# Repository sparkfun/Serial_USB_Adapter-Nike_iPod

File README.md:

**NOTE: This product has been retired from our catalog and is no longer for sale. This page is made available for those looking for datasheets and the simply curious.**

SparkFun Serial to USB Adapter - Nike+iPod
========================================

[*SparkFun Serial to USB Adapter - Nike+iPod (DEV-08245)*](https://www.sparkfun.com/products/8245)

This is a simple USB serial interface to mate with the Nike+iPod product. 
Use this breakout board to send and receive serial commands to the receiver and listen for individual foot pods. 
This will allow easy creation of proximity based projects and running/workout research. 
VCC (3.3V), ground, and iPod TX and RX are brought out to a standard header so that you can connect this board to a microcontroller.

Repository Contents
-------------------

* **/Firmware** - Example code 
* **/Hardware** - Eagle design files (.brd, .sch)
* **/Production** - Production panel files (.brd)

Documentation
--------------
* **[Hookup Guide](https://www.sparkfun.com/tutorials/41)** - Basic hookup guide for the adapter.
* **[SparkFun Fritzing repo](https://github.com/sparkfun/Fritzing_Parts)** - Fritzing diagrams for SparkFun products.
* **[SparkFun 3D Model repo](https://github.com/sparkfun/3D_Models)** - 3D models of SparkFun products. 

License Information
-------------------
This product is _**open source**_! 

The **hardware** is released under [Creative Commons ShareAlike 4.0 International](https://creativecommons.org/licenses/by-sa/4.0/).

Please use, reuse, and modify these files as you see fit. Please maintain attribution to SparkFun Electronics and release anything derivative under the same license.

Distributed as-is; no warranty is given.

- Your friends at SparkFun.

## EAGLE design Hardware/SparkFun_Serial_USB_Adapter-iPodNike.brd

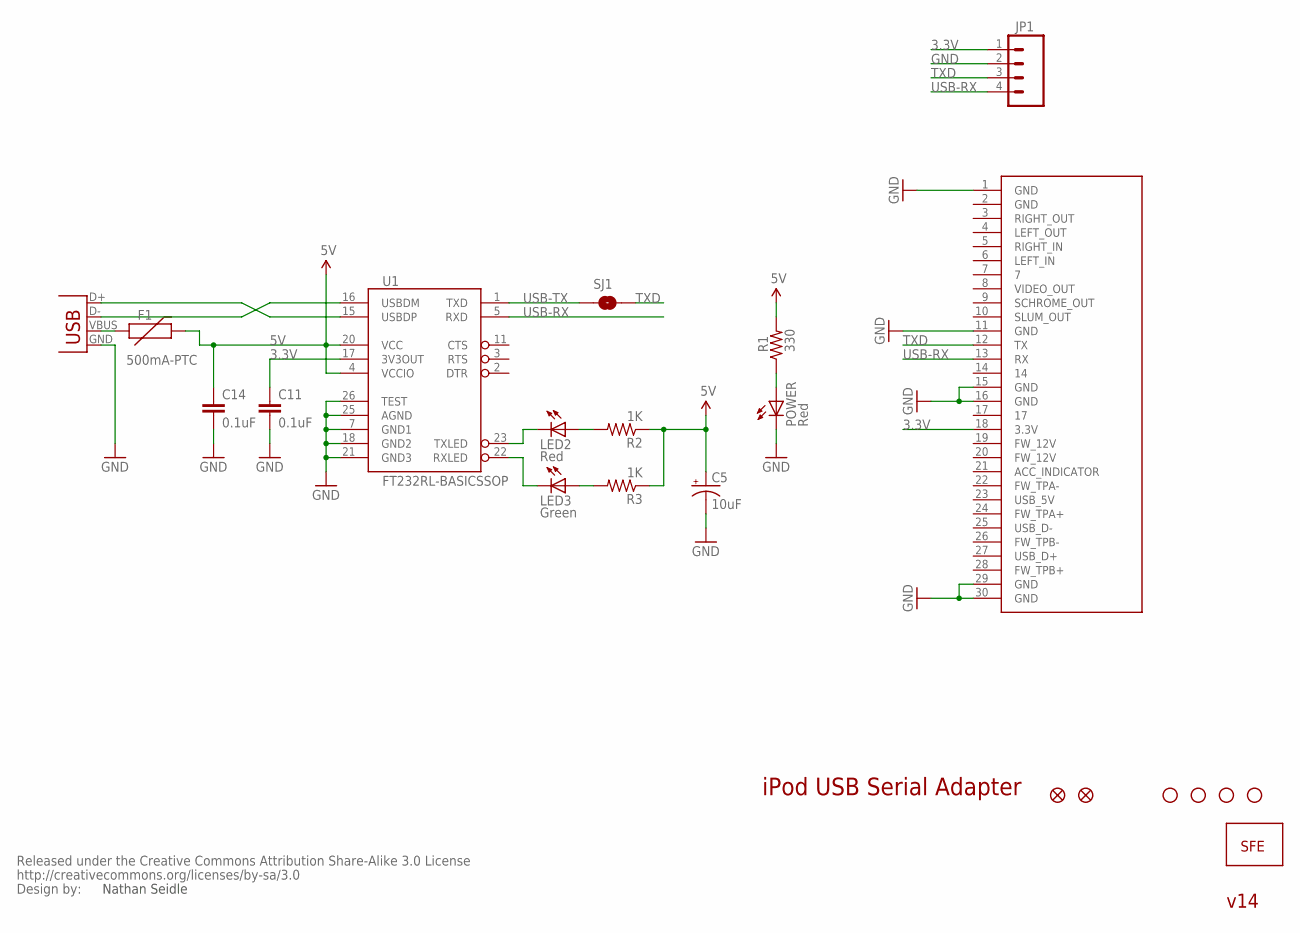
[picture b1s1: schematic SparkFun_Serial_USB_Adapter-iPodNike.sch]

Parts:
C5: 10uF; EIA3216
C11, C14: 0.1uF; C0402
F1: 500mA-PTC; PTC-1206
JP1: M04PTH; 1X04
LED2: Red; LED-0603
LED3: Green; LED-0603
POWER: Red; LED-0603
R1: 330; C0402
R2, R3: 1K; C0402
SJ1: SOLDERJUMPERNC2; SJ_2S
U1: FT232RL-BASICSSOP; SSOP28DB
U$1, U$5, U$6, U$7: STAND-OFF
U$2: IPOD_CONNECTOR_FEMALE; IPOD_FEMALE_CONNECTOR
U$3: LOGO-SFENEW; SFE-NEW-WEBLOGO
U$4, U$8: FIDUCIAL1X2; FIDUCIAL-1X2
U$9: CREATIVE_COMMONS
X1: USBSMD; USB-MINIB

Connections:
3.3V: C11.1, JP1.1, U1.17 (3V3OUT), U$2.18 (3.3V)
5V: C5.A (+), C14.1, F1.2, R1.2, R2.1, R3.1, U1.4 (VCCIO), U1.20 (VCC)
GND: C5.C (-), C11.2, C14.2, JP1.2, POWER.C, U1.7 (GND1), U1.18 (GND2), U1.21 (GND3), U1.25 (AGND), U1.26 (TEST), U$2.1 (GND), U$2.11 (GND), U$2.15 (GND), U$2.16 (GND), U$2.29 (GND), U$2.30 (GND), X1.GND
unnamed: POWER.A, R1.1
unnamed: U1.15 (USBDP), X1.D+
unnamed: LED2.A, R2.2
unnamed: LED3.A, R3.2
unnamed: U1.16 (USBDM), X1.D-
RXLED: LED3.C, U1.22 (RXLED)
TXD: JP1.3, SJ1.2, U$2.12 (TX)
TXLED: LED2.C, U1.23 (TXLED)
USB-RX: JP1.4, U1.5 (RXD), U$2.13 (RX)
USB-TX: SJ1.1, U1.1 (TXD)
USBVCC: F1.1, X1.VBUS

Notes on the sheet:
iPod USB Serial Adapter
Nathan Seidle
v14

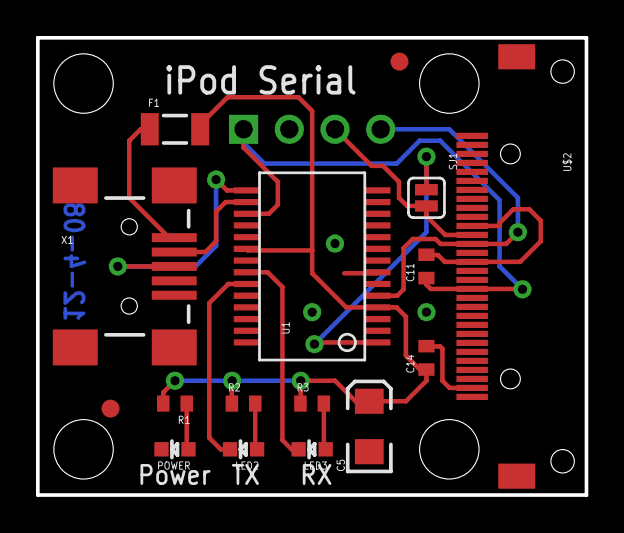
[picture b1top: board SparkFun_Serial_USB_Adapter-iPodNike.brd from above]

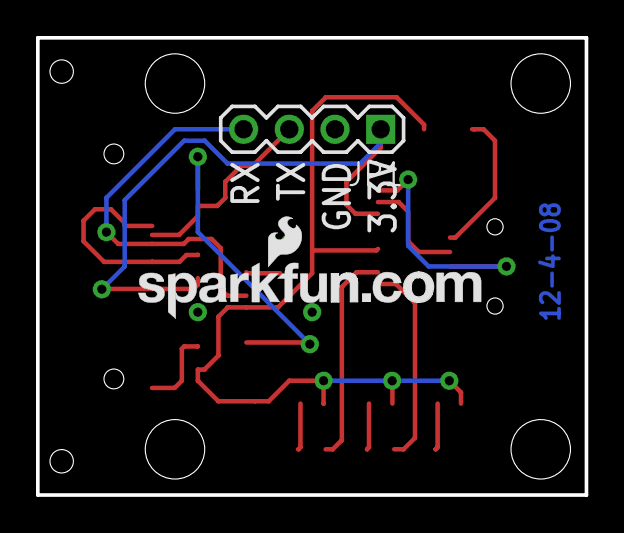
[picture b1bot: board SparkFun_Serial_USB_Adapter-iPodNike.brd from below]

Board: 2 copper layers, 30.5 x 25.4 mm, 23 parts (2 on the bottom side), 14 nets.

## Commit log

2015-05-12 Adding hardware files, example VB
2015-07-20 Update README.md
    Adding retired note.

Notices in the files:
parts and their libraries:
SparkFun: Released under the Creative Commons Attribution Share-Alike 3.0 License
SparkFun: http://creativecommons.org/licenses/by-sa/3.0
